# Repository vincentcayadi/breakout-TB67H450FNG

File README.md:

---
name: "Vincent Cayadi"
slack_handle: "@vincentcayadi"
github_handle: "@vincentcayadi"
---

# breakout-TB67H450FNG

The TB67H450FNG Breakout/Evaluation Board is a custom-designed board for the Toshiba TB67H450FNG motor driver IC. The datasheet for this component can be found [here](https://toshiba.semicon-storage.com/info/TB67H450FNG_datasheet_en_20201126.pdf?did=65346&prodName=TB67H450FNG).

This board is ideal for low-power robotics applications that require minimal torque, with a maximum current rating of 3.0A and a typical current rating of 1.5A. While the board features Surface Mounted Devices (SMD) components, soldering is relatively straightforward, making it accessible to a wide range of users.

I have designed the components using [KiCAD EDA](https://www.kicad.org/), a free EDA software.

## Bill-Of-Materials

| Part        | Quantity |             Description             |                                           Link                                            |
| :---------- | :------: | :---------------------------------: | :---------------------------------------------------------------------------------------: |
| TB67H450FNG |    1     | Toshiba TB67H450FNG Motor Driver IC | https://www.mouser.sg/ProductDetail/Toshiba/TB67H450FNGEL?qs=h6V4JsTaLXeReNg2bp0jug%3D%3D |

## Schematic

## PCB

## PCB Render

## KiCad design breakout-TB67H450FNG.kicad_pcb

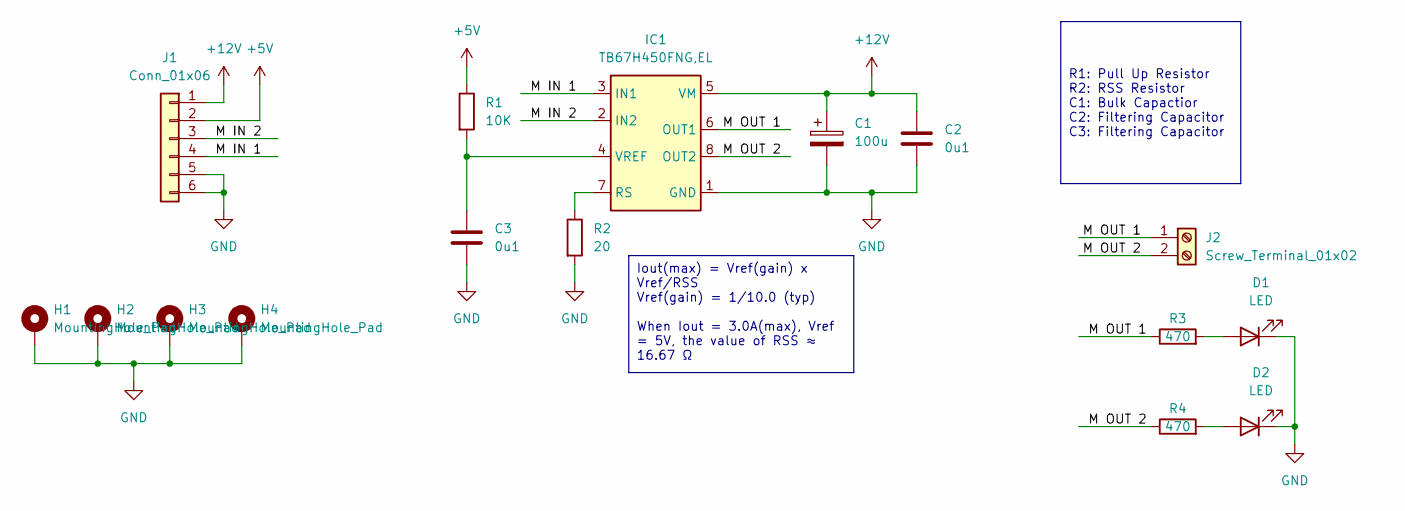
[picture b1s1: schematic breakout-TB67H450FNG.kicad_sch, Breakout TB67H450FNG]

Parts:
C1: 100u; CP_Radial_D8.0mm_P3.50mm
C2, C3: 0u1; cap0603
D1, D2: LED; led0603
H1, H2, H3, H4: MountingHole_Pad; MountingHole_3.2mm_M3_Pad_Via
IC1: TB67H450FNG,EL; P-HSOP8-0405-1p27-001_TOS; Mouser Part Number 757-TB67H450FNGEL
J1: Conn_01x06; PinSocket_1x06_P2.54mm_Vertical
J2: Screw_Terminal_01x02; xt30-f
R1: 10K; res0603
R2: 20; res0603
R3, R4: 470; res0603

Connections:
+5V: J1.2, R1.1
+12V: C1.1, C2.1, IC1.5 (VM), J1.1
/M IN 1: IC1.3 (IN1), J1.4
/M IN 2: IC1.2 (IN2), J1.3
/M OUT 1: IC1.6 (OUT1), J2.1, R3.1
/M OUT 2: IC1.8 (OUT2), J2.2, R4.1
GND: C1.2, C2.2, C3.2, D1.1 (K), D2.1 (K), H1.1, H2.1, H3.1, H4.1, IC1.1 (GND), IC1.9 (EP), J1.5, J1.6, R2.2
unnamed: D1.2 (A), R3.2
unnamed: D2.2 (A), R4.2
unnamed: IC1.7 (RS), R2.1
unnamed: C3.1, IC1.4 (VREF), R1.2

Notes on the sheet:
Iout(max) = Vref(gain) x Vref/RSS Vref(gain) = 1/10.0 (typ) When Iout = 3.0A(max), Vref = 5V, the value of RSS ≈ 16.67 Ω
R1: Pull Up Resistor R2: RSS Resistor C1: Bulk Capactior C2: Filtering Capacitor C3: Filtering Capacitor

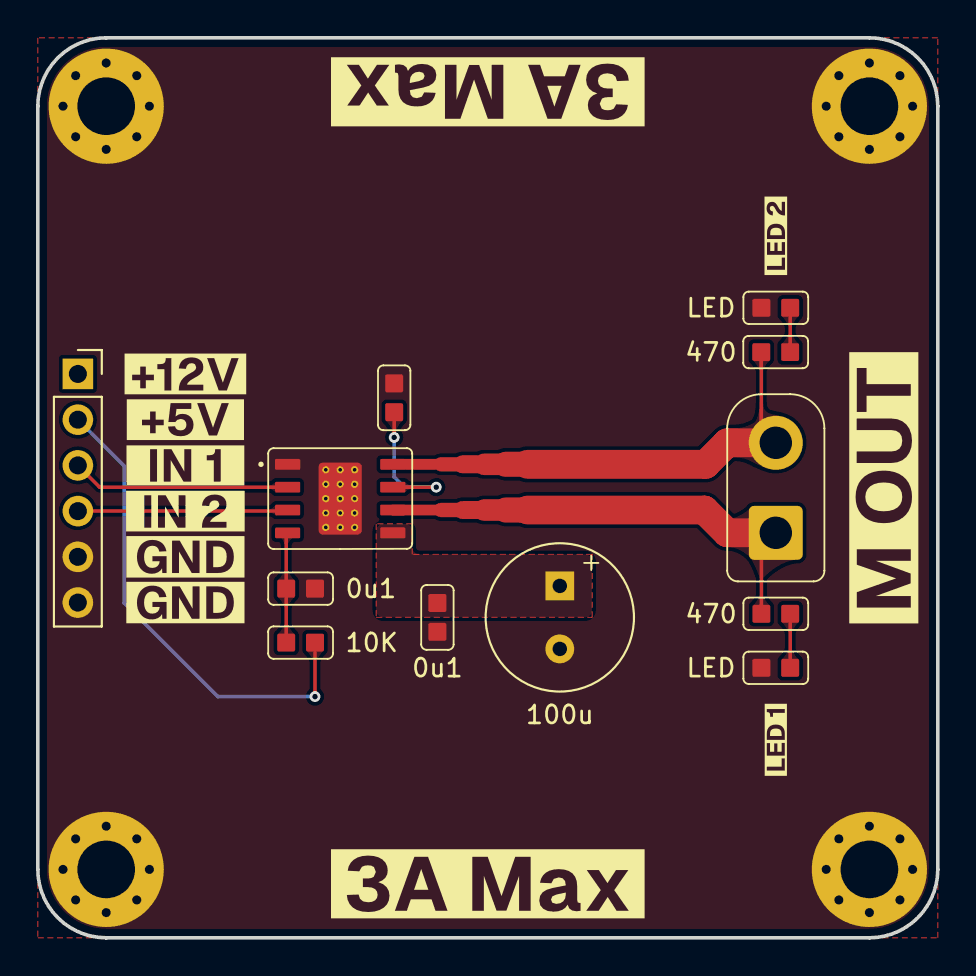
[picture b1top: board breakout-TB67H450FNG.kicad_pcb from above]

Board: 2 copper layers, 50.0 x 50.0 mm, 27 parts (0 on the bottom side), 11 nets.

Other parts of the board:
kibuzzard-66A14E1C: G***; kibuzzard-66A14E1C
kibuzzard-66A14E9E: G***; kibuzzard-66A14E9E
kibuzzard-66A14E66: G***; kibuzzard-66A14E66
kibuzzard-66A14E76: G***; kibuzzard-66A14E76
kibuzzard-66A14EA3: G***; kibuzzard-66A14EA3
kibuzzard-66A150A6: G***; kibuzzard-66A150A6
kibuzzard-66A150AD: G***; kibuzzard-66A150AD
kibuzzard-66A15010: G***; kibuzzard-66A15010
kibuzzard-66A15016: G***; kibuzzard-66A15016
kibuzzard-66A15073: G***; kibuzzard-66A15073
kibuzzard-66A15093: G***; kibuzzard-66A15093

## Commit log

2024-07-24 Inital Commit
2024-07-24 uploaded image to readme
2024-07-24 changed image
2024-07-24 schametic image
2024-07-24 Changed Footpint, Added DEBUG LED, Layouted PCB
2024-07-25 Almost close to finishing
2024-07-25 Gerber
